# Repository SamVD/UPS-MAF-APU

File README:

#this is the MAF UPS project
schematic, board, and order form for tssop-16 breakout board

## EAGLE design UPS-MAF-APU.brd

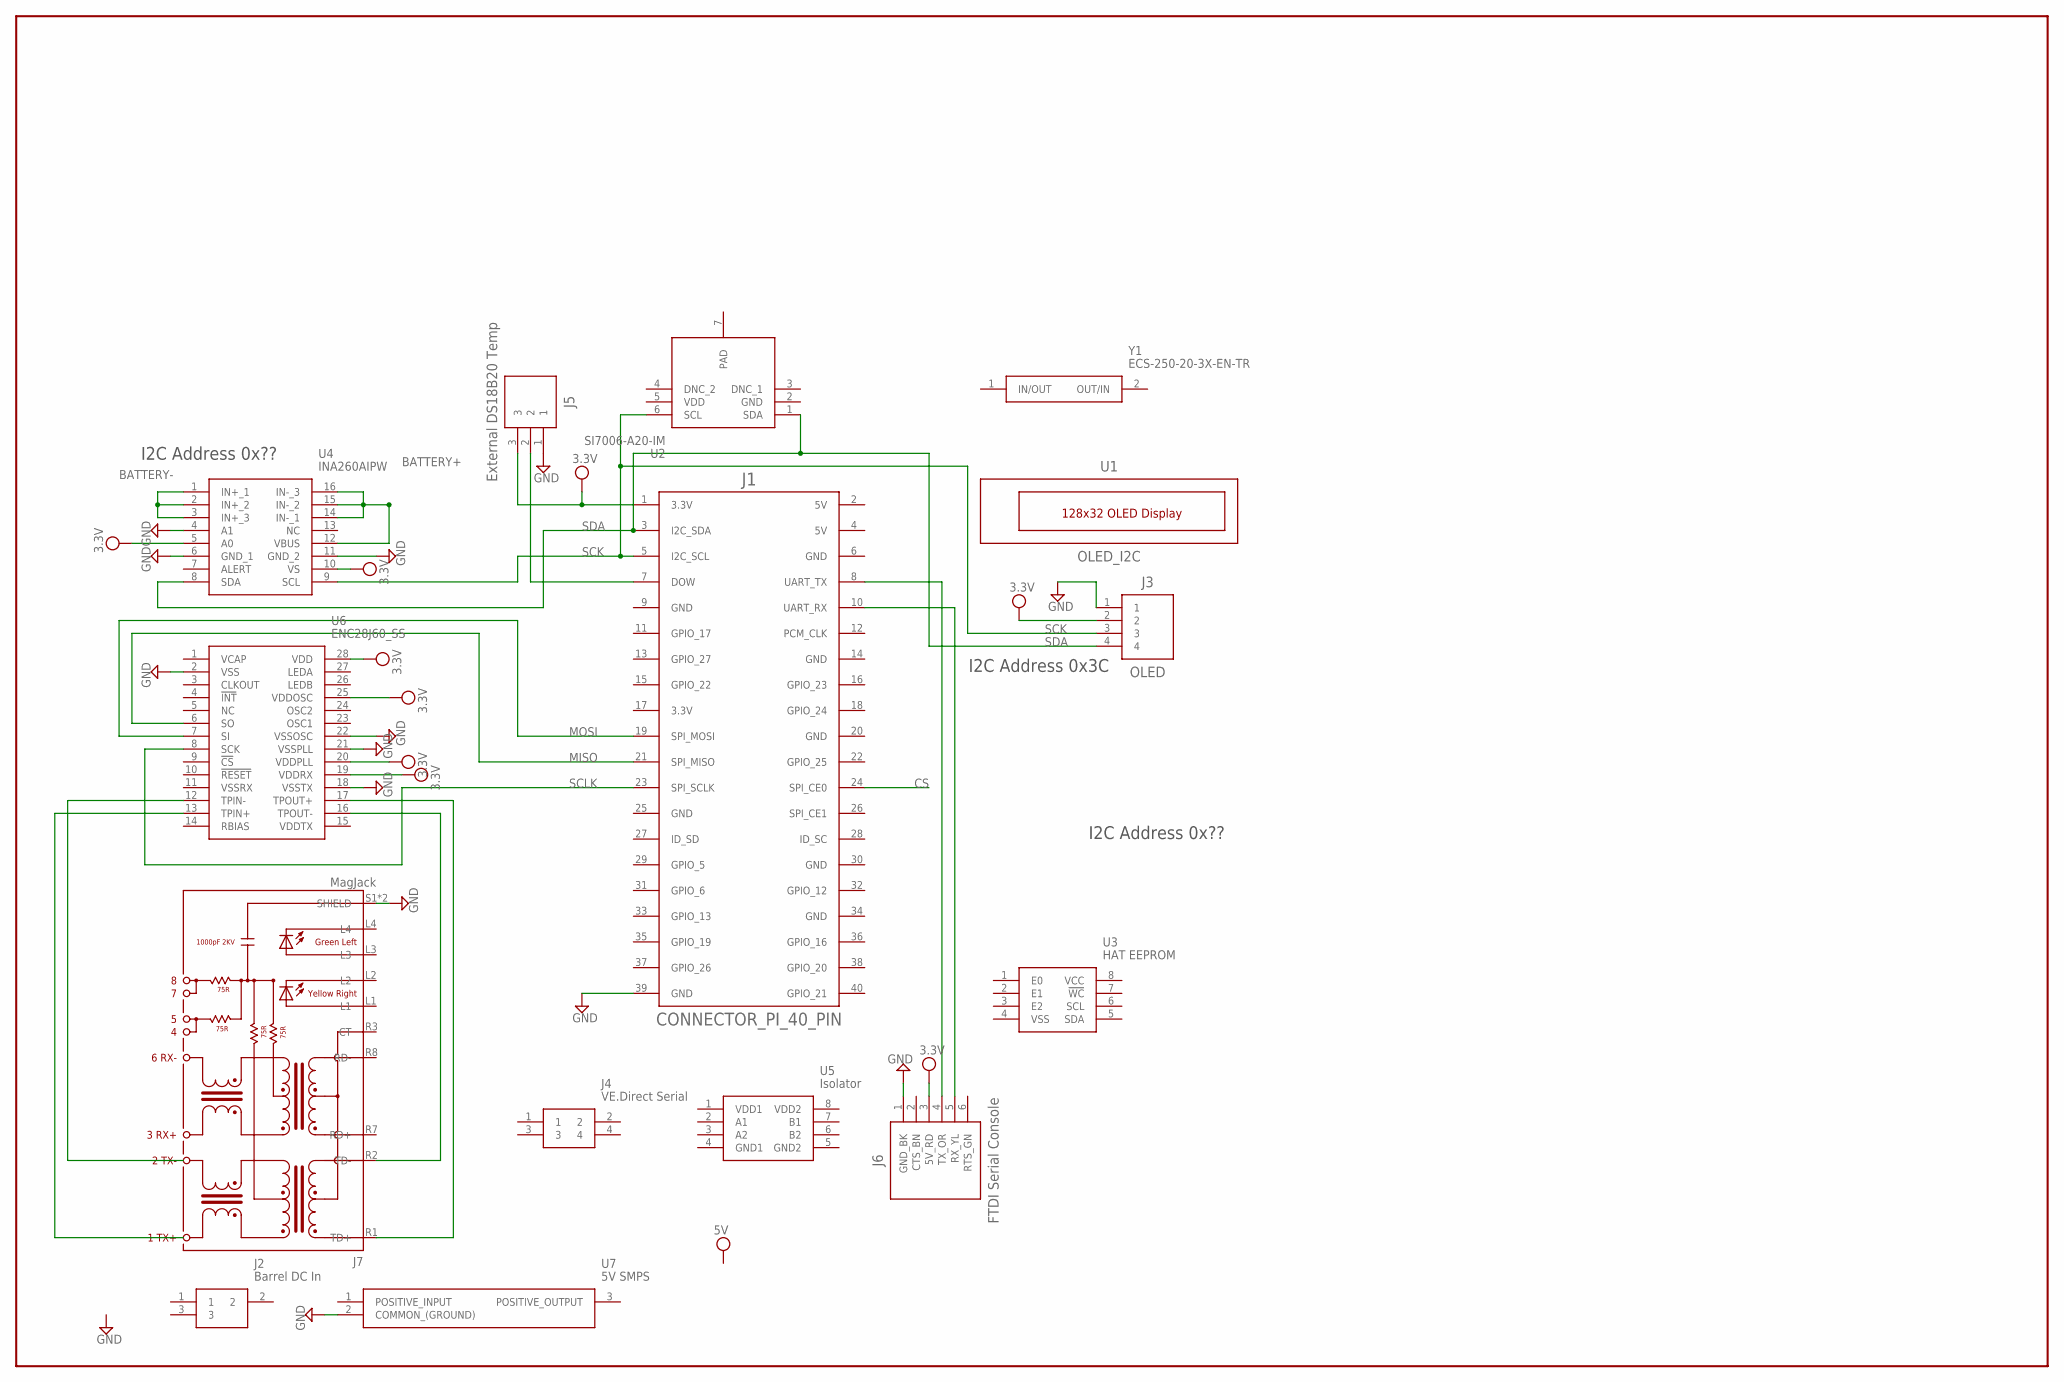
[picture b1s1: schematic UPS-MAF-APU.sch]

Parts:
J1: CONNECTOR_PI_40_PIN; 2X20
J2: Barrel DC In; PJ-102AH
J3: OLED; ESQ-104-XX-X-S
J4: VE.Direct Serial; S4B-PH-SM4-TB
J5: External DS18B20 Temp; MOLEX_70553-0002
J6: FTDI Serial Console; ESQ-106-XX-X-S
J7: MagJack; WIZNET_RB1-125BAG1A
U1: OLED_I2C; OLED-I2C
U2: SI7006-A20-IM; SON100P300X300X80-7N
U3: HAT EEPROM; SOP65P640X120-8N
U4: INA260AIPW; SOP65P640X120-16N
U5: Isolator; SOIC127P600X175-8N
U6: ENC28J60_SS; SOP65P780X200-28N
U7: 5V SMPS; OKI-78SR-HORIZONTAL
Y1: ECS-250-20-3X-EN-TR; ECS250203XENTR

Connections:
3.3V: J1.1 (3.3V), J3.2, J5.3, J6.3 (5V_RD), U4.5 (A0), U4.10 (VS), U6.19 (VDDRX), U6.20 (VDDPLL), U6.25 (VDDOSC), U6.28 (VDD)
BATTERY+: U4.12 (VBUS), U4.14 (IN-_1), U4.15 (IN-_2), U4.16 (IN-_3)
BATTERY-: U4.1 (IN+_1), U4.2 (IN+_2), U4.3 (IN+_3)
CS: J1.24 (SPI_CE0)
GND: J1.39 (GND), J3.1, J5.1, J6.1 (GND_BK), J7.S1 (SHIELD), J7.S2 (SHIELD), U2.2 (GND), U4.4 (A1), U4.6 (GND_1), U4.11 (GND_2), U6.2 (VSS), U6.18 (VSSTX), U6.21 (VSSPLL), U6.22 (VSSOSC), U7.2 (COMMON_(GROUND))
MISO: J1.21 (SPI_MISO), U6.6 (SO)
MOSI: J1.19 (SPI_MOSI), U6.7 (SI)
unnamed: J1.8 (UART_TX), J6.4 (TX_OR)
unnamed: J1.10 (UART_RX), J6.5 (RX_YL)
unnamed: J1.7 (DOW), J5.2
unnamed: J7.R2 (TD-), U6.16 (TPOUT-)
unnamed: J7.R1 (TD+), U6.17 (TPOUT+)
PAD: U2.7 (PAD)
SCK: J1.5 (I2C_SCL), J3.3, U2.6 (SCL), U4.9 (SCL)
SCLK: J1.23 (SPI_SCLK), U6.8 (SCK)
SDA: J1.3 (I2C_SDA), J3.4, U2.1 (SDA), U4.8 (SDA)
VDD: U2.5 (VDD)
VDDTX: U6.15 (VDDTX)
VSSRX: U6.11 (VSSRX)

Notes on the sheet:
I2C Address 0x3C
I2C Address 0x??

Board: 2 copper layers, 15 parts (0 on the bottom side), 14 nets, no tracks yet.

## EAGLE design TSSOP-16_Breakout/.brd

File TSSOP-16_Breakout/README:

These files are the total package necessary for seeing the TSSOP-16 breakout board for the MAF UPS project. It has the order form from
OshPark and also schematic and board

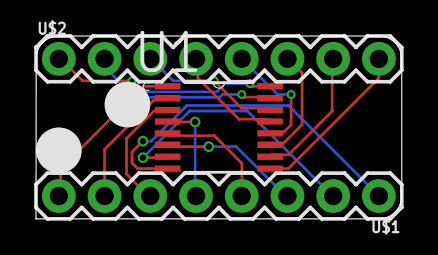
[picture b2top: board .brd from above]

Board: 2 copper layers, 20.3 x 10.2 mm, 3 parts (0 on the bottom side), 16 nets.

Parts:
U1: INA-260; SOP65P640X110-16N
U$1, U$2: 8_PIN_CONN; 1X08

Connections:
unnamed: U1.8, U$1.1
unnamed: U1.7, U$1.2
unnamed: U1.6, U$1.3
unnamed: U1.5, U$1.4
unnamed: U1.4, U$1.5
unnamed: U1.3, U$1.6
unnamed: U1.2, U$1.7
unnamed: U1.1, U$1.8
unnamed: U1.16, U$2.1
unnamed: U1.15, U$2.2
unnamed: U1.14, U$2.3
unnamed: U1.13, U$2.4
unnamed: U1.12, U$2.5
unnamed: U1.11, U$2.6
unnamed: U1.10, U$2.7
unnamed: U1.9, U$2.8

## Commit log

2019-01-25 add blank EAGLE library
2019-01-25 add SOP65P640X110-16N TSSOP-16 footprint, donwnloaded from SnapEDA part LM5574MT
2019-01-25 UPDATED_LIB
2019-02-04 Add files via upload
    1 x 1.39 in. - 16 prong breakout board - rendered and manufactured by OshPark. Created by Sam V.D.
2019-02-05 Eagle Library
2019-02-18 Create Orderlink
2019-02-26 add many parts to library
    Raspberry Pi 40-pin connector, 128x32 I2C OLED, 3.3, 5, GND nets, letter landscape frame.
2019-02-26 add schematic and board
2019-03-01 add more to-do items for schematic
2019-03-03 Add parts to library, Schematic. Add barrel power jack, INA260 I/V sensor, 5V Murata SMPS. Change parts to UPS library.
2019-03-03 Add tons of parts to Library and Schematic, update symbol styles.
2019-03-03 Add parts to schematic, change to Tabloid size page/frame.
2019-03-04 SamChange
    editpush?
2019-03-07 README
2019-03-24 Update and rename UPS-MAF-APU.sch to UPS-MAF-APU-scehmatic-previous
